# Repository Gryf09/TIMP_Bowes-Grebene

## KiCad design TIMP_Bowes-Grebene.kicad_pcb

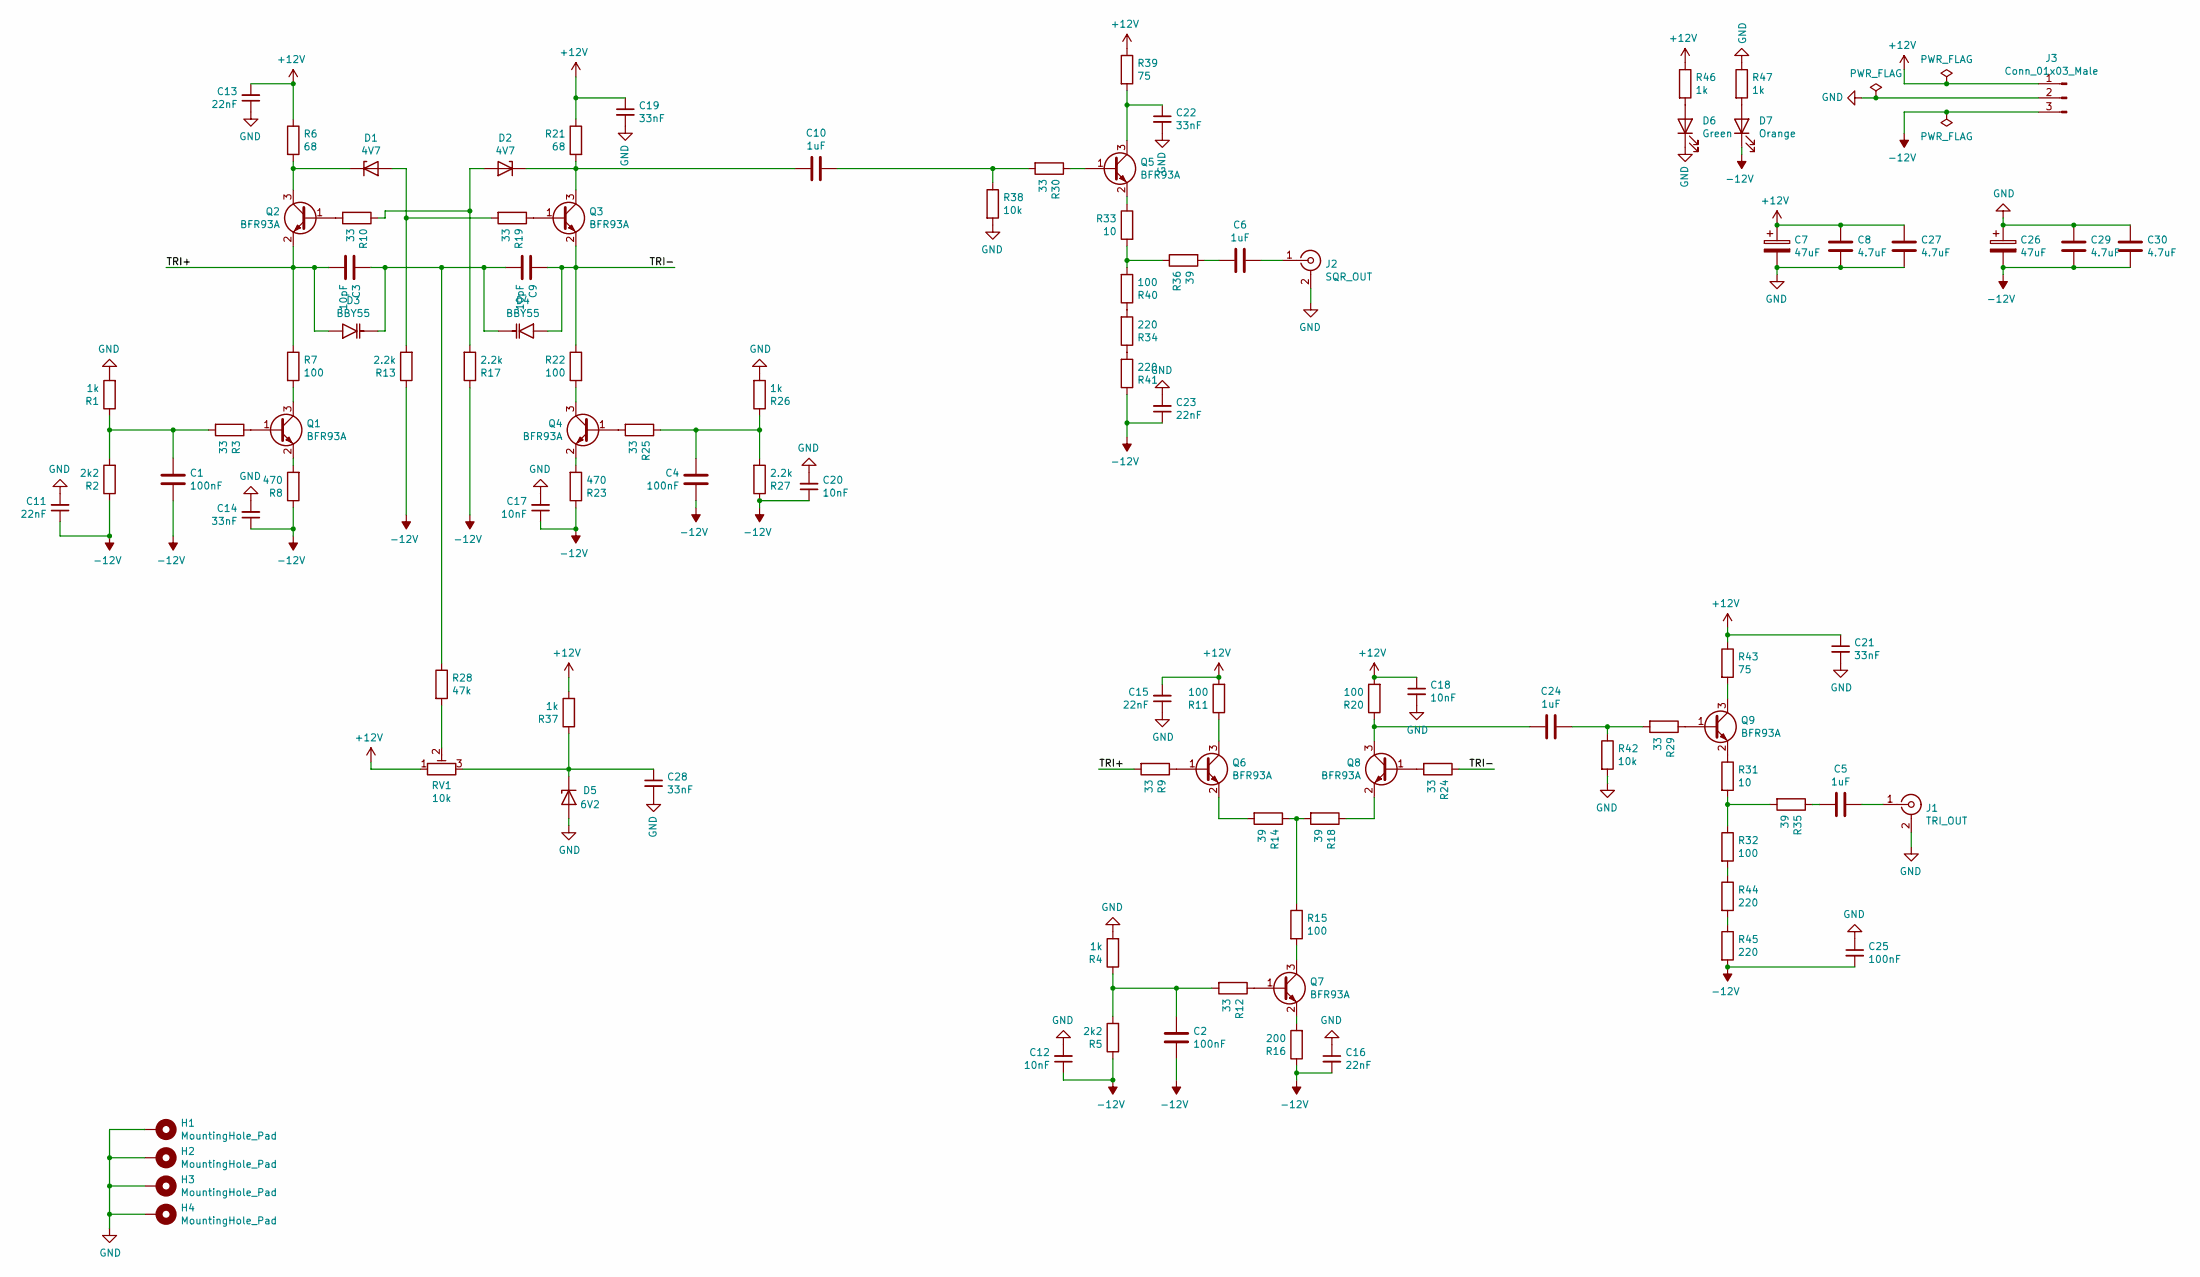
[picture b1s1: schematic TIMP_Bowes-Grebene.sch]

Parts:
C1, C2, C4, C25: 100nF; C_0805_2012Metric
C3, C9: 10pF; C_0805_2012Metric
C5, C6, C10, C24: 1uF; C_1206_3216Metric
C7, C26: 47uF; CP_Elec_8x6.2
C8, C27, C29, C30: 4.7uF; C_1206_3216Metric
C11, C13, C15, C16, C23: 22nF; C_0805_2012Metric
C12, C17, C18, C20: 10nF; C_0805_2012Metric
C14, C19, C21, C22, C28: 33nF; C_0805_2012Metric
D1, D2: 4V7; D_SOD-123
D3, D4: BBY55; D_SOD-523
D5: 6V2; D_SOD-123
D6: Green; LED_1206_3216Metric
D7: Orange; LED_1206_3216Metric
H1, H2, H3, H4: MountingHole_Pad; MountingHole_3.2mm_M3_Pad_Via
J1: TRI_OUT; BNC_Amphenol_B6252HB-NPP3G-50_Horizontal
J2: SQR_OUT; BNC_Amphenol_B6252HB-NPP3G-50_Horizontal
J3: Conn_01x03_Male; PinHeader_1x03_P2.54mm_Vertical
Q1, Q2, Q3, Q4, Q5, Q6, Q7, Q8, Q9: BFR93A; SOT-23
R1, R4, R26, R37, R46, R47: 1k; R_0805_2012Metric
R2, R5: 2k2; R_0805_2012Metric
R3, R9, R10, R12, R19, R24, R25, R29, R30: 33; R_0805_2012Metric
R6, R21: 68; R_0805_2012Metric
R7, R11, R15, R20, R22, R32, R40: 100; R_0805_2012Metric
R8, R23: 470; R_0805_2012Metric
R13, R17, R27: 2.2k; R_0805_2012Metric
R14, R18, R35, R36: 39; R_0805_2012Metric
R16: 200; R_0805_2012Metric
R28: 47k; R_0805_2012Metric
R31, R33: 10; R_0805_2012Metric
R34, R41, R44, R45: 220; R_1206_3216Metric
R38, R42: 10k; R_0805_2012Metric
R39, R43: 75; R_0805_2012Metric
RV1: 10k; Potentiometer_ACP_CA9-H5_Horizontal

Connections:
+12V: C7.1, C8.2, C13.2, C15.2, C18.1, C19.1, C21.1, C27.2, J3.1, R6.1, R11.2, R20.2, R21.1, R37.2, R39.1, R43.1, R46.1, RV1.1
-12V: C1.2, C2.2, C4.2, C11.1, C12.1, C14.1, C16.2, C17.1, C20.1, C23.1, C25.2, C26.2, C29.1, C30.1, D7.1 (K), J3.3, R2.1, R5.1, R8.1, R13.1, R16.1, R17.1, R23.1, R27.1, R41.1, R45.2
/TRI+: C3.2, D3.2 (A), Q2.2 (E), R7.1, R9.2
/TRI-: C9.1, D4.2 (A), Q3.2 (E), R22.1, R24.1
GND: C7.2, C8.1, C11.2, C12.2, C13.1, C14.2, C15.1, C16.1, C17.2, C18.2, C19.2, C20.2, C21.2, C22.2, C23.2, C25.1, C26.1, C27.1, C28.2, C29.2, C30.2, D5.2 (A), D6.1 (K), H1.1, H2.1, H3.1, H4.1, J1.2 (Ext), J2.2 (Ext), J3.2, R1.2, R4.2, R26.2, R38.2, R42.2, R47.1
unnamed: C1.1, R1.1, R2.2, R3.2
unnamed: C2.1, R4.1, R5.2, R12.2
unnamed: C3.1, C9.2, D3.1 (K), D4.1 (K), R28.1
unnamed: C4.1, R25.1, R26.1, R27.2
unnamed: C5.1, J1.1 (In)
unnamed: C5.2, R35.1
unnamed: C6.1, J2.1 (In)
unnamed: C6.2, R36.2
unnamed: C10.1, R30.2, R38.1
unnamed: C10.2, D2.1 (K), Q3.3 (C), R21.2
unnamed: C22.1, Q5.3 (C), R39.2
unnamed: C24.1, R29.2, R42.1
unnamed: C24.2, Q8.3 (C), R20.1
unnamed: C28.1, D5.1 (K), R37.1, RV1.3
unnamed: D1.1 (K), Q2.3 (C), R6.2
unnamed: D1.2 (A), R13.2, R19.2
unnamed: D2.2 (A), R10.1, R17.2
unnamed: D6.2 (A), R46.2
unnamed: D7.2 (A), R47.2
unnamed: Q1.1 (B), R3.1
unnamed: Q1.2 (E), R8.2
unnamed: Q1.3 (C), R7.2
unnamed: Q2.1 (B), R10.2
unnamed: Q3.1 (B), R19.1
unnamed: Q4.1 (B), R25.2
unnamed: Q4.2 (E), R23.2
unnamed: Q4.3 (C), R22.2
unnamed: Q5.1 (B), R30.1
unnamed: Q5.2 (E), R33.1
unnamed: Q6.1 (B), R9.1
unnamed: Q6.2 (E), R14.2
unnamed: Q6.3 (C), R11.1
unnamed: Q7.1 (B), R12.1
unnamed: Q7.2 (E), R16.2
unnamed: Q7.3 (C), R15.2
unnamed: Q8.1 (B), R24.2
unnamed: Q8.2 (E), R18.1
unnamed: Q9.1 (B), R29.1
unnamed: Q9.2 (E), R31.1
unnamed: Q9.3 (C), R43.2
unnamed: R14.1, R15.1, R18.2
unnamed: R28.2, RV1.2
unnamed: R31.2, R32.1, R35.2
unnamed: R32.2, R44.1
unnamed: R33.2, R36.1, R40.2
unnamed: R34.1, R41.2
unnamed: R34.2, R40.1
unnamed: R44.2, R45.1

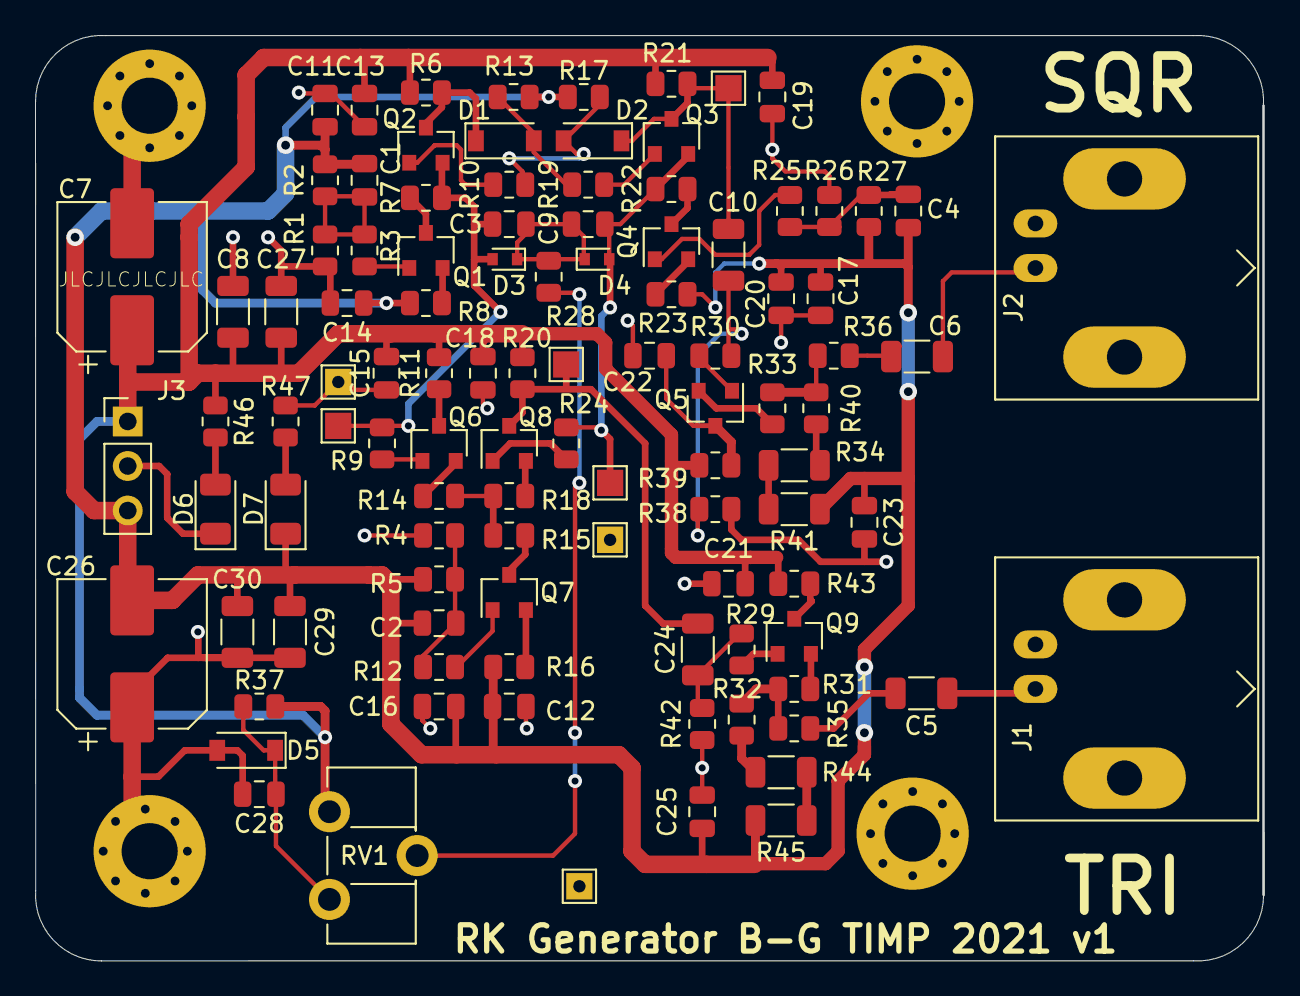
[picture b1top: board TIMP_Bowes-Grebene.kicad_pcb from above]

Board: 2 copper layers, 70.0 x 52.7 mm, 101 parts (0 on the bottom side), 53 nets.
